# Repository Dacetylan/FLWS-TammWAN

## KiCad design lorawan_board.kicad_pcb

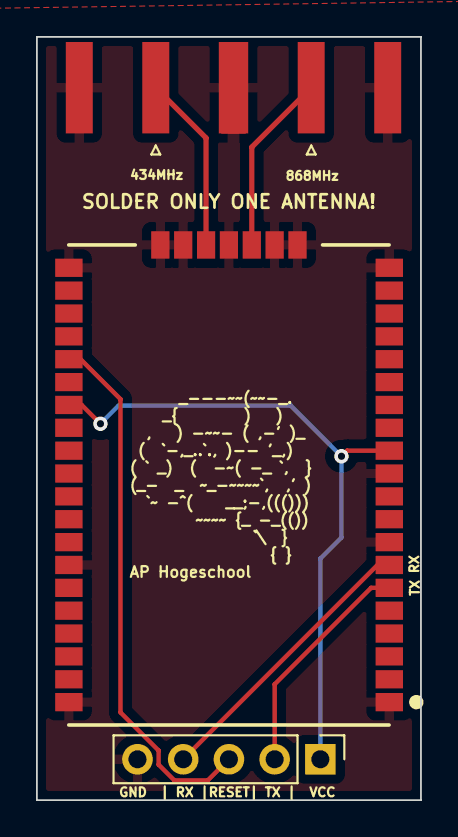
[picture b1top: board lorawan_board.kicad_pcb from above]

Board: 2 copper layers, 21.3 x 42.4 mm, 4 parts (0 on the bottom side), 7 nets.

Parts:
J1: Conn_01x05; PinHeader_1x05_P2.54mm_Vertical
J2, J3: Conn_Coaxial; SMA_Amphenol_132289_EdgeMount
U1: RN2483

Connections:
434MHz: J2.1 (In), U1.25 (RFL)
868MHz: J3.1 (In), U1.23 (RFH)
GND: J1.5, J2.2 (Ext), J3.2 (Ext), U1.1 (GND_1), U1.8 (GND_2), U1.11 (GND_3), U1.20 (GND_4), U1.21 (GND_5), U1.22 (GND_6), U1.24 (GND_7), U1.26 (GND_8), U1.27 (GND_9), U1.28 (GND_10), U1.33 (GND_11), U1.41 (GND_12), U1.47 (GND_13)
RESET: J1.3, U1.32 (~RESET)
RX: J1.4, U1.7 (UART_RX)
TX: J1.2, U1.6 (UART_TX)
VCC: J1.1, U1.12 (VDD_1), U1.34 (VDD_2)

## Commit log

2022-10-11 smaller board'
2022-10-11 removed backups folder
